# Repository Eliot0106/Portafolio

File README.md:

# Portafolio de Proyectos de Eliot Izquierdo Balencia

¡Hola! 👋 Bienvenido a mi portafolio de ingeniería. Soy un apasionado de la robótica, el control automático y el diseño mecánico.

Este repositorio sirve como una colección centralizada de mis proyectos académicos y personales más relevantes, demostrando mis habilidades en la creación de soluciones desde el concepto y el diseño CAD hasta la implementación de hardware (PCB) y software (firmware).

---

## 🚀 Habilidades y Tecnologías

Aquí hay un resumen de las tecnologías y habilidades que encontrarás en mis proyectos:

* **Diseño Electrónico (EDA):** Diseño de PCBs en **KiCad**, selección de componentes (reguladores, drivers, microcontroladores).
* **Diseño Mecánico (CAD):** Diseño de chasis y mecanismos en **SolidWorks**.
* **Simulación de Circuitos:** Análisis de configuraciones (serie, paralelo, mixto) en **Proteus**.
* **Fabricación Digital:** Impresión 3D (FDM) para prototipado rápido de chasis y piezas mecánicas.
* **Programación (Firmware):** C++ (para **Arduino** / **ESP32**), Python.
* **Control y Robótica:** Algoritmos de **Cinemática Inversa (IK)**, Control de Procesos (Térmico), Algoritmos de Navegación (Wall-Follower), control de motores (Puentes H, Servos).
* **Sensores:** Integración de Termopares (SPI), Sensores ToF (I2C), Sensores Analógicos (IR).
* **Análisis y Simulación (FEA):** Experiencia básica en simulación de esfuerzos y análisis estático en **SolidWorks Simulation**.

---

## 📂 Índice de Proyectos

Navega por las carpetas para ver los detalles, el código y la documentación técnica de cada proyecto.

### 1. Proyectos Escolares (School Proyects)
Proyectos desarrollados durante mi formación en el **CETI**, enfocados en la aplicación práctica de la teoría de control e instrumentación.

* **[Horno](./School%20Proyects/Horno)**
    * **Descripción:** Diseño y construcción de un horno eléctrico para calentar alimentos (lasaña) en el menor tiempo posible, aplicando la **Ley de Joule**. Se realizó un análisis de circuitos en Proteus para optimizar la configuración de las resistencias.
    * **Habilidades:** Control de procesos térmicos (Control ON-OFF con histéresis de $\pm5^{\circ}C$) , integración de hardware de potencia (Relés, Termopar Tipo K vía SPI), HMI (LCD I2C) y construcción refractaria.
aa
* **[Maze_Robot](./School%20Proyects/Maze_Robot)**
    * **Descripción:** Robot autónomo diseñado para resolver laberintos. Utiliza un algoritmo de **seguimiento de pared (wall-follower)**  que prioriza giros basado en la data de múltiples sensores.
    * **Habilidades:** Fusión de sensores (Láser ToF VL53L0X para detección frontal , IR Analógicos CNY70 para detección lateral y de suelo), programación de algoritmos de navegación y control de motores PWM.

* **[Robot_3DOF](./School%20Proyects/Robot_3DOF)**
    * **Descripción:** Implementación de un algoritmo de **Cinemática Inversa (IK)** geométrica  para controlar un brazo robótico de 3 Grados de Libertad (GDL) mediante coordenadas cartesianas (X, Y, Z).
    * **Habilidades:** Matemáticas aplicadas (Ley de Cosenos) , programación de algoritmos de control, SolidWorks.

* **[Reactor_Batch](./School%20Proyects/Reactor_Batch)**
    * **Descripción:** Automatización de un reactor químico batch a escala. Incluye un dispensador de pastillas (piñón-cremallera) diseñado en CAD e impreso en 3D, y un sistema de agitación y bombeo controlado por Arduino.
    * **Habilidades:** Control de procesos, diseño mecánico (engranajes), integración de hardware (servos, bombas), HMI (LCD I2C).

* **[Sumo_Rob_10x10 / 20x20](./School%20Proyects/Sumo_Rob_10x10)**
    * **Descripción:** Diseño integral (hardware y software) de un robot de sumo de competencia.Se diseñó un chasis optimizado (centro de gravedad bajo)y una PCB personalizada en KiCad para integrar los sensores (VL53L0X) y los drivers de motor.
    * **Habilidades:** Diseño de PCB (KiCad), diseño de chasis (Impresión 3D), integración de sensores (I2C), gestión de potencia.

### 2. Diseños Mecánicos (Mechanical Design)
Una colección de diseños conceptuales y prácticos realizados en SolidWorks, enfocados en la manufactura y el ensamblaje.

* **[Sumo_Designs](./Mechanical%20Design/Sumo_Designs)**
    * **Descripción:** Conceptos y prototipos de chasis para robots de sumo, optimizados para impresión 3D y bajo centro de gravedad.
* **[UGV Chassis Concept](./Mechanical%20Design/UGV%20Chassis%20Concept)**
    * **Descripción:** Concepto de un chasis para un Vehículo Terrestre No Tripulado (UGV), enfocado en la modularidad y resistencia.
* **[Closet](./Mechanical%20Design/Closet)**
    * **Descripción:** Diseño de mobiliario (clóset) enfocado en la optimización de espacio y ensamblaje.
* **[Practice](./Mechanical%20Design/Practice)**
    * **Descripción:** Archivos de práctica y ejercicios varios de modelado en SolidWorks.

---

## 📫 Contacto
* **Email:** eliotizq@gmail.com
* **LinkedIn:** www.linkedin.com/in/eliot-izquierdo-85326a372

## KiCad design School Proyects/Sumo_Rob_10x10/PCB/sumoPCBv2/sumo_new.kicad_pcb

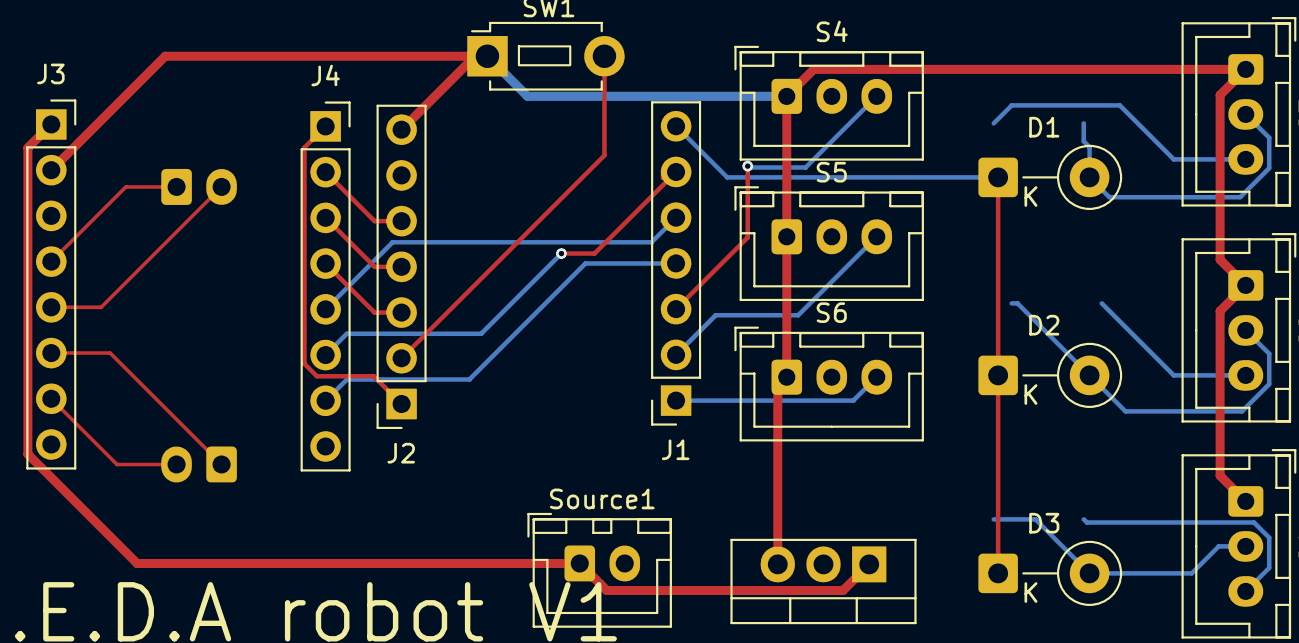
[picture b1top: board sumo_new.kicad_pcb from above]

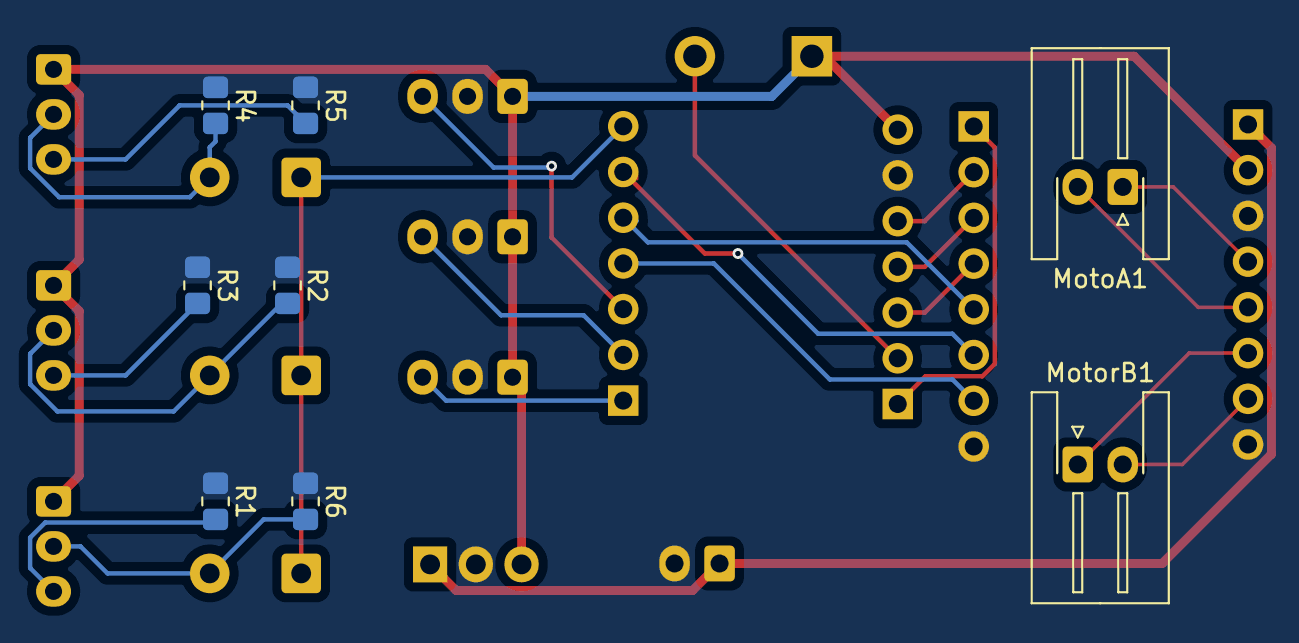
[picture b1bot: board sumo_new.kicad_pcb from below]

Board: 2 copper layers, 24 parts (8 on the bottom side), 25 nets.

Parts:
D1, D2, D3: 1N4001; D_DO-41_SOD81_P5.08mm_Vertical_KathodeUp
J1, J2: Conn_01x07_Socket; PinSocket_1x07_P2.54mm_Vertical
J3, J4: Conn_01x08_Socket; PinSocket_1x08_P2.54mm_Vertical
MotoA1: Conn_01x02_Socket; JST_XH_S2B-XH-A-1_1x02_P2.50mm_Horizontal
MotorB1: Conn_01x02_Socket; JST_XH_S2B-XH-A-1_1x02_P2.50mm_Horizontal
R1, R3, R5: 330; R_0805_2012Metric_Pad1.20x1.40mm_HandSolder
R2, R4, R6: 10k; R_0805_2012Metric_Pad1.20x1.40mm_HandSolder
S1, S2, S3, S4, S5, S6: Conn_01x03_Socket; JST_XH_B3B-XH-A_1x03_P2.50mm_Vertical
SW1: SW_Push; SW_PUSH_1P1T_6x3.5mm_H5.0_APEM_MJTP1250
Source1: Conn_01x02_Socket; JST_XH_B2B-XH-A_1x02_P2.50mm_Vertical
U2: LM7805_TO220; TO-220-3_Vertical

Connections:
+5V: J2.7, J3.2, S1.1, S2.1, S3.1, S4.1, S5.1, S6.1, SW1.1, U2.3 (VO)
+10V: J3.1, Source1.1, U2.1 (VI)
/MA1: J2.5, J4.2
/MA2: J2.4, J4.3
/MB1: J1.5, J4.5
/MB2: J1.6, J4.6
/PWMA: J2.1, J4.1
/PWMB: J1.4, J4.7
/S1: D3.2 (A), R6.2, S1.2
/S2: D2.2 (A), R2.2, S2.2
/S3: D1.2 (A), R4.2, S3.2
/S4: J1.3, S4.3
/S5: J1.2, S5.3
/S6: J1.1, S6.3
/Stby: J2.3, J4.4
GND: J2.6, J3.3, J3.8, J4.8, R1.1, R2.1, R3.1, R4.1, R5.1, R6.1, S4.2, S5.2, S6.2, Source1.2, U2.2 (GND)
unnamed: D1.1 (K), D2.1 (K), D3.1 (K), J1.7
unnamed: J2.2, SW1.2
unnamed: J3.4, MotoA1.1
unnamed: J3.5, MotoA1.2
unnamed: J3.6, MotorB1.1
unnamed: J3.7, MotorB1.2
unnamed: R1.2, S1.3
unnamed: R3.2, S2.3
unnamed: R5.2, S3.3

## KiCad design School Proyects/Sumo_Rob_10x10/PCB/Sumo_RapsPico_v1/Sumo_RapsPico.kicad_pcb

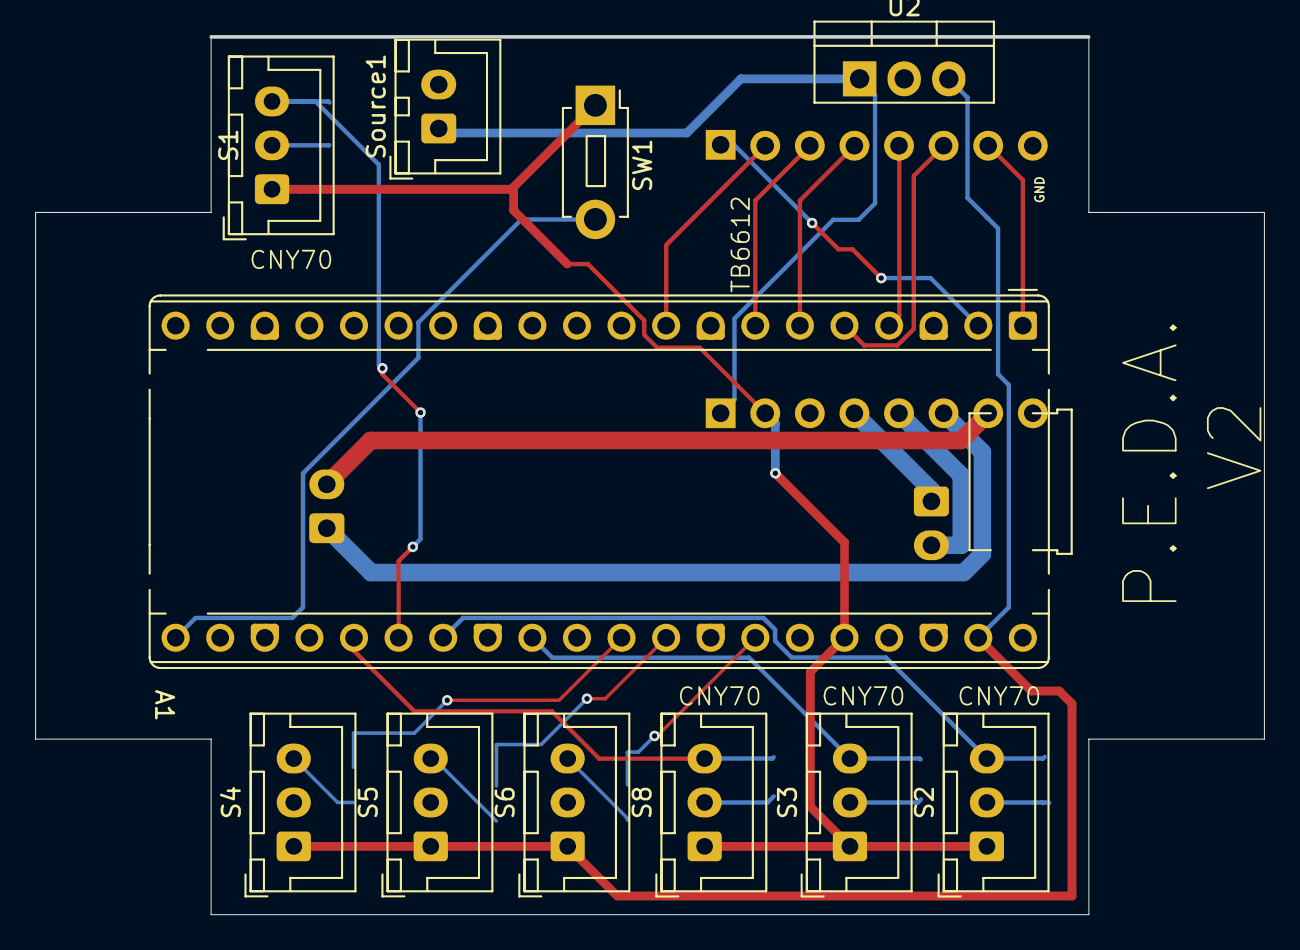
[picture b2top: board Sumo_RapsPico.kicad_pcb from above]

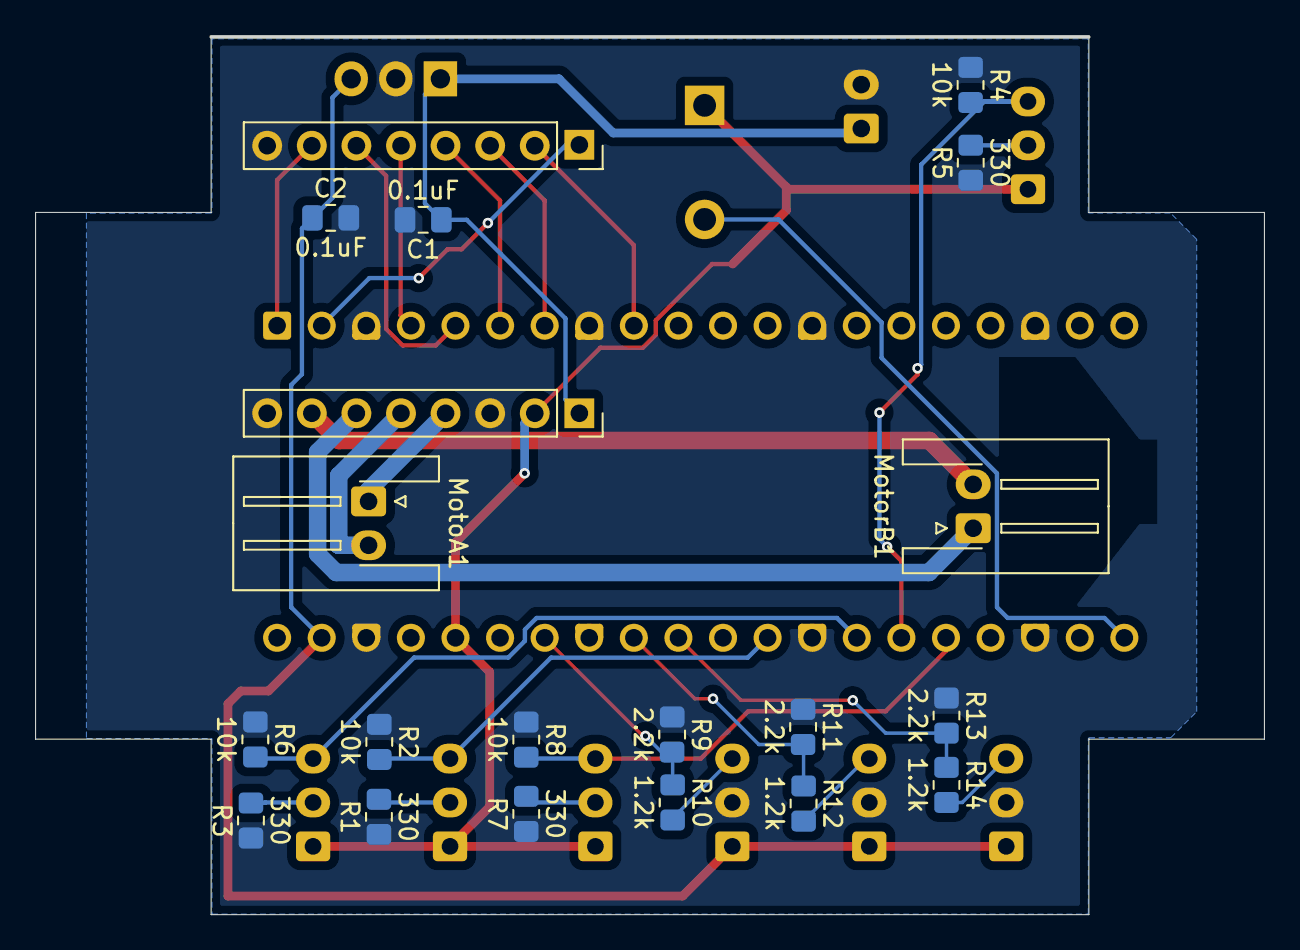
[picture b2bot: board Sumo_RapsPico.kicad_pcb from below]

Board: 2 copper layers, 69.9 x 49.9 mm, 31 parts (20 on the bottom side), 30 nets.

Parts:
A1: RaspberryPi_Pico; RaspberryPi_Pico_Common_THT
C1, C2: 0.1uF; C_0805_2012Metric_Pad1.18x1.45mm_HandSolder
J3, J4: Conn_01x08_Socket; PinSocket_1x08_P2.54mm_Vertical
MotoA1: Conn_01x02_Socket; JST_XH_S2B-XH-A-1_1x02_P2.50mm_Horizontal
MotorB1: Conn_01x02_Socket; JST_XH_S2B-XH-A-1_1x02_P2.50mm_Horizontal
R1, R3, R5, R7: 330; R_0805_2012Metric_Pad1.20x1.40mm_HandSolder
R2, R4, R6, R8: 10k; R_0805_2012Metric_Pad1.20x1.40mm_HandSolder
R9, R11, R13: 2.2k; R_0805_2012Metric_Pad1.20x1.40mm_HandSolder
R10, R12, R14: 1.2k; R_0805_2012Metric_Pad1.20x1.40mm_HandSolder
S1, S2, S3, S4, S5, S6, S8: Conn_01x03_Socket; JST_XH_B3B-XH-A_1x03_P2.50mm_Vertical
SW1: SW_Push; SW_PUSH_1P1T_6x3.5mm_H5.0_APEM_MJTP1250
Source1: Conn_01x02_Socket; JST_XH_B2B-XH-A_1x02_P2.50mm_Vertical
U2: LM7805_TO220; TO-220-3_Vertical

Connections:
+3.3V: A1.36 (3V3), J3.2, S1.1, S2.1, S3.1, S8.1, SW1.1
+5V: A1.39 (VSYS), C2.1, S4.1, S5.1, S6.1, U2.3 (VO)
+10V: C1.1, J3.1, Source1.1, U2.1 (VI)
/MA1: A1.9 (GPIO6), J4.2
/MA2: A1.7 (GPIO5), J4.3
/MB1: A1.4 (GPIO2), J4.5
/MB2: A1.5 (GPIO3), J4.6
/PWMA: A1.2 (GPIO1), J4.1
/PWMB: A1.1 (GPIO0), J4.7
/S1: A1.26 (GPIO20), R4.2, S1.3
/S2: A1.27 (GPIO21), R6.2, S2.3
/S3: A1.29 (GPIO22), R2.2, S3.3
/S4: A1.31 (GPIO26_ADC0), R13.2, R14.1
/S5: A1.32 (GPIO27_ADC1), R11.2, R12.1
/S6: A1.34 (GPIO28_ADC2), R9.2, R10.1
/S8: A1.25 (GPIO19), R8.2, S8.3
/Stby: A1.6 (GPIO4), J4.4
GND: A1.3 (GND), A1.8 (GND), A1.13 (GND), A1.18 (GND), A1.23 (GND), A1.28 (GND), A1.38 (GND), C1.2, C2.2, J3.3, J3.8, J4.8, R1.1, R2.1, R3.1, R4.1, R5.1, R6.1, R7.1, R8.1, R9.1, R11.1, R13.1, S4.2, S5.2, S6.2, Source1.2, U2.2 (GND)
unnamed: A1.21 (GPIO16), SW1.2
unnamed: J3.4, MotoA1.1
unnamed: J3.5, MotoA1.2
unnamed: J3.6, MotorB1.1
unnamed: J3.7, MotorB1.2
unnamed: R5.2, S1.2
unnamed: R3.2, S2.2
unnamed: R1.2, S3.2
unnamed: R14.2, S4.3
unnamed: R12.2, S5.3
unnamed: R10.2, S6.3
unnamed: R7.2, S8.2

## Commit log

2025-11-06 Primera carga de trabajos
2025-11-06 SE agregan proyectos escolares relevantes(video de Brazon robot en README
2025-11-06 README.md
    Resumen de repositorio
